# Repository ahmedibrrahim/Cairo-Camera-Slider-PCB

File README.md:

# Cairo-Camera-Slider-PCB
For someone who loves to shoot some random hobbyist videos, it’s somehow expensive to buy a motorized camera slider. So, I built my own. Here's the PCB Eagle Project
Full project ste-by-step tutorial: https://makesomestuff.org/arduino-motorized-camera-slider/

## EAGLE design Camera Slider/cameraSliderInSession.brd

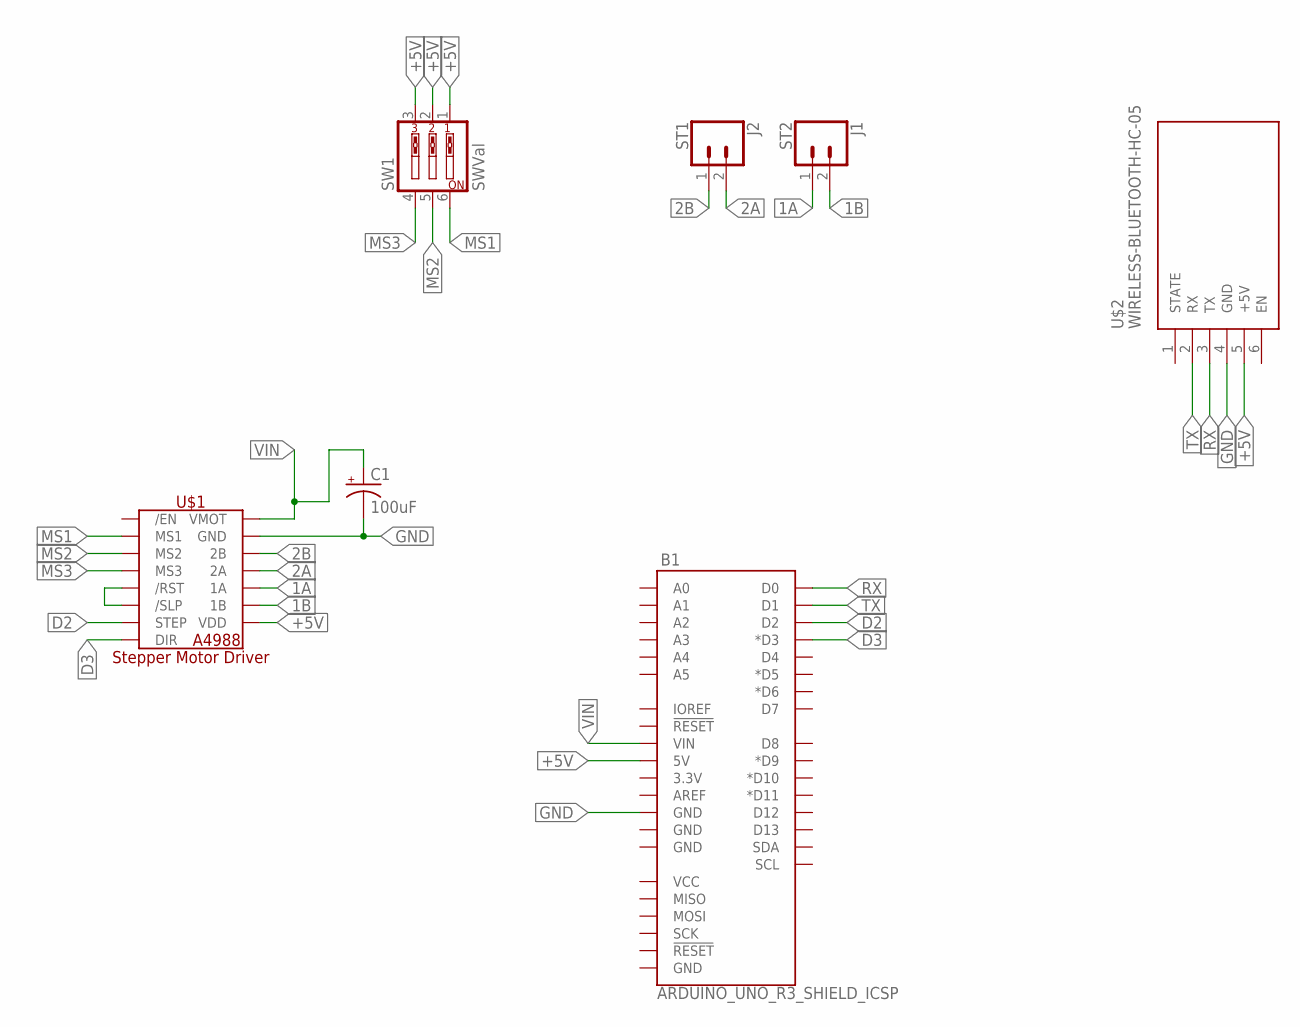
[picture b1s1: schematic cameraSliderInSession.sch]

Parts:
B1: ARDUINO_UNO_R3_SHIELD_ICSP; UNO_R3_SHIELD_ICSP
C1: 100uF; CPOL-RADIAL-2.5MM-6.5MM
J1: ST2; SCREWTERMINAL-5MM-2
J2: ST1; SCREWTERMINAL-5MM-2
SW1: SWVal; EDG-03
U$1: A4988_STEP
U$2: WIRELESS-BLUETOOTH-HC-05

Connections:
1A: J1.1, U$1.1A
1B: J1.2, U$1.1B
2A: J2.2, U$1.2A
2B: J2.1, U$1.2B
+5V: B1.5V, SW1.1, SW1.2, SW1.3, U$1.VDD, U$2.5 (+5V)
D2: B1.D2, U$1.STEP
D3: B1.D3 (*D3), U$1.DIR
GND: B1.GND@2 (GND), C1.2 (-), U$1.GND, U$1.GND2 (GND), U$2.4 (GND)
MS1: SW1.6, U$1.MS1
MS2: SW1.5, U$1.MS2
MS3: SW1.4, U$1.MS3
unnamed: U$1./RST, U$1./SLP
RX: B1.RX (D0), U$2.3 (TX)
TX: B1.TX (D1), U$2.2 (RX)
VIN: B1.VIN, C1.1 (+), U$1.VMOT

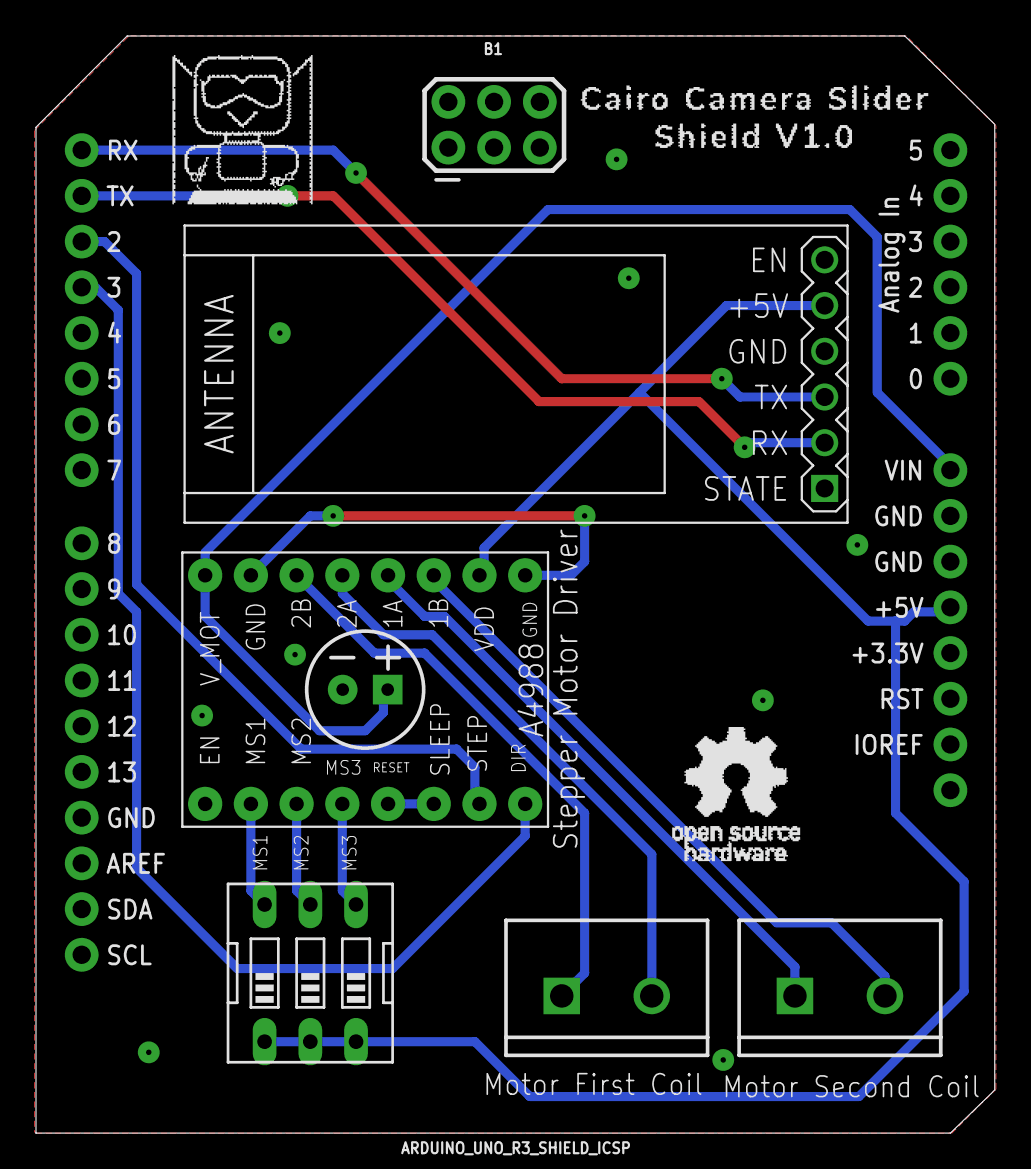
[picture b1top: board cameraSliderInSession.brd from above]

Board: 2 copper layers, 53.3 x 61.0 mm, 7 parts (0 on the bottom side), 15 nets.

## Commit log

2020-02-28 Initial Upload
2021-01-23 adding tutorial link

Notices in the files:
parts and their libraries:
SparkFun-Boards: Licensing: Creative Commons ShareAlike 4.0 International - https://creativecommons.org/licenses/by-sa/4.0
diy-modules: Released under the Creative Commons Attribution 4.0 International License: http://creativecommons.org/licenses/by/4.0
